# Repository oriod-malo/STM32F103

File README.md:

# STM32F103 Custom Kit

My first PCB project in KiCad. 

A custom STM32F103 kit with header pins, USB connector and LED.

Very useful to get handy with KiCad.

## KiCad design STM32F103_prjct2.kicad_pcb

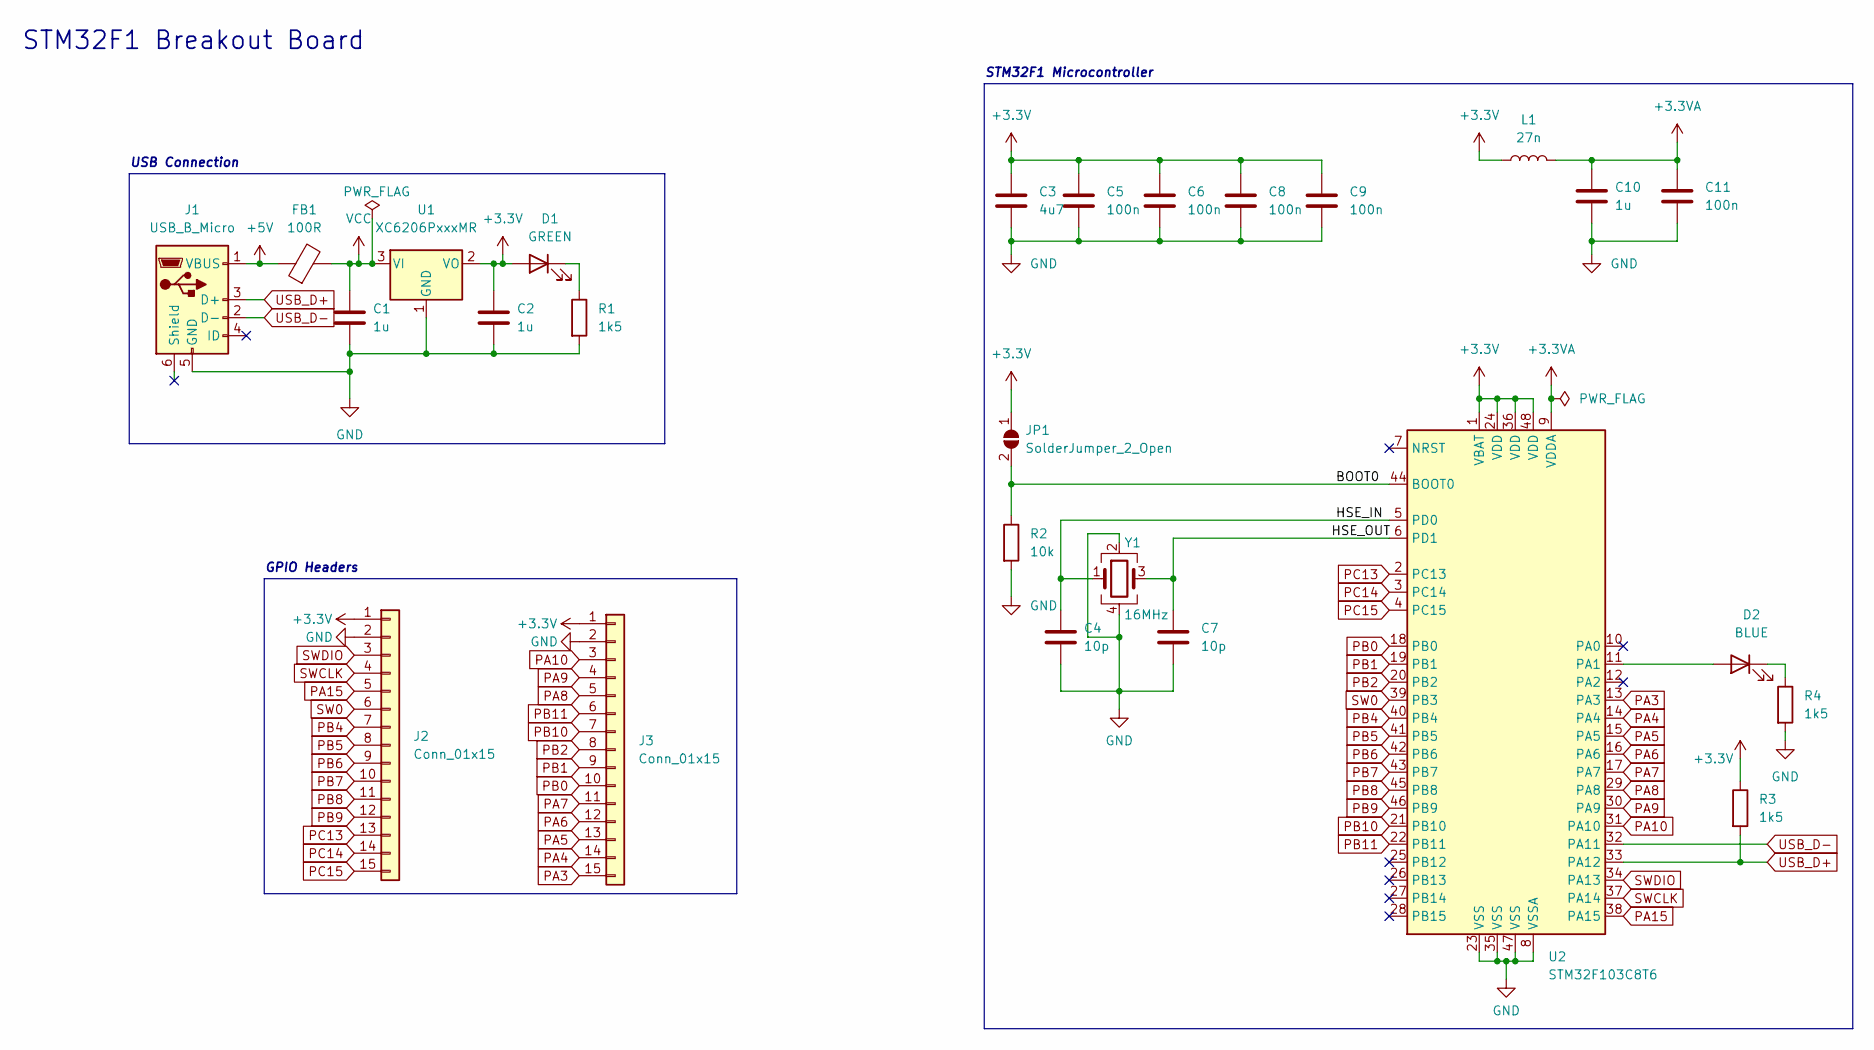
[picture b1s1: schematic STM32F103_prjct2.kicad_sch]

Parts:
C1, C2: 1u; C_0603_1608Metric
C3: 4u7; C_0603_1608Metric
C4, C7: 10p; C_0402_1005Metric
C5, C6, C8, C9, C11: 100n; C_0402_1005Metric
C10: 1u; C_0402_1005Metric
D1: GREEN; LED_0603_1608Metric
D2: BLUE; LED_0603_1608Metric
FB1: 100R; L_0805_2012Metric
J1: USB_B_Micro; USB_Micro-B_Wuerth_629105150521
J2, J3: Conn_01x15; PinHeader_1x15_P2.54mm_Vertical
JP1: SolderJumper_2_Open; SolderJumper-2_P1.3mm_Open_Pad1.0x1.5mm
L1: 27n; L_0402_1005Metric
R1, R3: 1k5; R_0603_1608Metric
R2: 10k; R_0402_1005Metric
R4: 1k5; R_0402_1005Metric
U1: XC6206PxxxMR; SOT-23
U2: STM32F103C8T6; LQFP-48_7x7mm_P0.5mm
Y1: 16MHz; Crystal_SMD_3225-4Pin_3.2x2.5mm

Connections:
+3.3V: C2.1, C3.1, C5.1, C6.1, C8.1, C9.1, D1.2 (A), J2.1, J3.1, JP1.1 (A), L1.1, R3.1, U1.2 (VO), U2.1 (VBAT), U2.24 (VDD), U2.36 (VDD), U2.48 (VDD)
+3.3VA: C10.1, C11.1, L1.2, U2.9 (VDDA)
+5V: FB1.1, J1.1 (VBUS)
/BOOT0: JP1.2 (B), R2.1, U2.44 (BOOT0)
/HSE_IN: C4.1, U2.5 (PD0), Y1.1
/HSE_OUT: C7.1, U2.6 (PD1), Y1.3
GND: C1.2, C2.2, C3.2, C4.2, C5.2, C6.2, C7.2, C8.2, C9.2, C10.2, C11.2, J1.5 (GND), J2.2, J3.2, R1.2, R2.2, R4.2, U1.1 (GND), U2.8 (VSSA), U2.23 (VSS), U2.35 (VSS), U2.47 (VSS), Y1.2, Y1.4
unnamed: D1.1 (K), R1.1
unnamed: D2.1 (K), R4.1
unnamed: D2.2 (A), U2.11 (PA1)
PA3: J3.15, U2.13 (PA3)
PA4: J3.14, U2.14 (PA4)
PA5: J3.13, U2.15 (PA5)
PA6: J3.12, U2.16 (PA6)
PA7: J3.11, U2.17 (PA7)
PA8: J3.5, U2.29 (PA8)
PA9: J3.4, U2.30 (PA9)
PA10: J3.3, U2.31 (PA10)
PA15: J2.5, U2.38 (PA15)
PB0: J3.10, U2.18 (PB0)
PB1: J3.9, U2.19 (PB1)
PB2: J3.8, U2.20 (PB2)
PB4: J2.7, U2.40 (PB4)
PB5: J2.8, U2.41 (PB5)
PB6: J2.9, U2.42 (PB6)
PB7: J2.10, U2.43 (PB7)
PB8: J2.11, U2.45 (PB8)
PB9: J2.12, U2.46 (PB9)
PB10: J3.7, U2.21 (PB10)
PB11: J3.6, U2.22 (PB11)
PC13: J2.13, U2.2 (PC13)
PC14: J2.14, U2.3 (PC14)
PC15: J2.15, U2.4 (PC15)
SW0: J2.6, U2.39 (PB3)
SWCLK: J2.4, U2.37 (PA14)
SWDIO: J2.3, U2.34 (PA13)
USB_D+: J1.3 (D+), R3.2, U2.33 (PA12)
USB_D-: J1.2 (D-), U2.32 (PA11)
VCC: C1.1, FB1.2, U1.3 (VI)

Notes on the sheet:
STM32F1 Microcontroller
USB Connection
GPIO Headers
STM32F1 Breakout Board

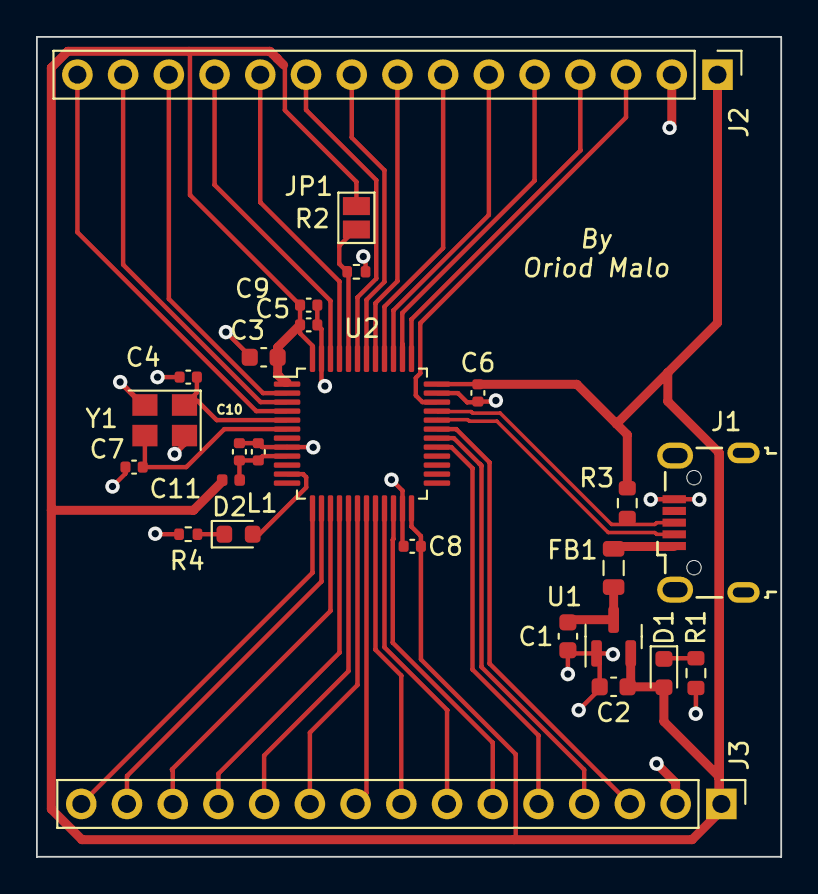
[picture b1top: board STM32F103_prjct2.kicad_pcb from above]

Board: 2 copper layers, 41.3 x 45.5 mm, 26 parts (0 on the bottom side), 39 nets.

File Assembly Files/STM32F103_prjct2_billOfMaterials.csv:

"Source:","C:\Users\CTS\Documents\KiCad\6.0\projects\STM32F103_prjct2\STM32F103_prjct2.kicad_sch"
"Date:","3/20/2023 7:13:50 PM"
"Tool:","Eeschema (6.0.9)"
"Generator:","C:\Program Files\KiCad\6.0\bin\scripting\plugins/bom_csv_grouped_by_value.py"
"Component Count:","26"

"Individual Components:"

"Item","Qty","Reference(s)","Value","LibPart","Footprint","Datasheet"
"","","C1","1u","Device:C","Capacitor_SMD:C_0603_1608Metric","~"
"","","C2","1u","Device:C","Capacitor_SMD:C_0603_1608Metric","~"
"","","C3","4u7","Device:C","Capacitor_SMD:C_0603_1608Metric","~"
"","","C4","10p","Device:C","Capacitor_SMD:C_0402_1005Metric","~"
"","","C5","100n","Device:C","Capacitor_SMD:C_0402_1005Metric","~"
"","","C6","100n","Device:C","Capacitor_SMD:C_0402_1005Metric","~"
"","","C7","10p","Device:C","Capacitor_SMD:C_0402_1005Metric","~"
"","","C8","100n","Device:C","Capacitor_SMD:C_0402_1005Metric","~"
"","","C9","100n","Device:C","Capacitor_SMD:C_0402_1005Metric","~"
"","","C10","1u","Device:C","Capacitor_SMD:C_0402_1005Metric","~"
"","","C11","100n","Device:C","Capacitor_SMD:C_0402_1005Metric","~"
"","","D1","GREEN","Device:LED","LED_SMD:LED_0603_1608Metric","~"
"","","D2","BLUE","Device:LED","LED_SMD:LED_0603_1608Metric","~"
"","","FB1","100R","Device:FerriteBead","Inductor_SMD:L_0805_2012Metric","~"
"","","J1","USB_B_Micro","Connector:USB_B_Micro","Connector_USB:USB_Micro-B_Wuerth_629105150521","~"
"","","J2","Conn_01x15","Connector_Generic:Conn_01x15","Connector_PinHeader_2.54mm:PinHeader_1x15_P2.54mm_Vertical","~"
"","","J3","Conn_01x15","Connector_Generic:Conn_01x15","Connector_PinHeader_2.54mm:PinHeader_1x15_P2.54mm_Vertical","~"
"","","JP1","SolderJumper_2_Open","Jumper:SolderJumper_2_Open","Jumper:SolderJumper-2_P1.3mm_Open_Pad1.0x1.5mm","~"
"","","L1","27n","Device:L","Inductor_SMD:L_0402_1005Metric","~"
"","","R1","1k5","Device:R","Resistor_SMD:R_0603_1608Metric","~"
"","","R2","10k","Device:R","Resistor_SMD:R_0402_1005Metric","~"
"","","R3","1k5","Device:R","Resistor_SMD:R_0603_1608Metric","~"
"","","R4","1k5","Device:R","Resistor_SMD:R_0402_1005Metric","~"
"","","U1","XC6206PxxxMR","Regulator_Linear:XC6206PxxxMR","Package_TO_SOT_SMD:SOT-23","https://www.torexsemi.com/file/xc6206/XC6206.pdf"
"","","U2","STM32F103C8T6","MCU_ST_STM32F1:STM32F103C8Tx","Package_QFP:LQFP-48_7x7mm_P0.5mm","http://www.st.com/st-web-ui/static/active/en/resource/techni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"
"","","Y1","16MHz","Device:Crystal_GND24","Crystal:Crystal_SMD_3225-4Pin_3.2x2.5mm","~"



"Collated Components:"

"Item","Qty","Reference(s)","Value","LibPart","Footprint","Datasheet"
"1","2","C1, C2","1u","Device:C","Capacitor_SMD:C_0603_1608Metric","~"
"2","1","C3","4u7","Device:C","Capacitor_SMD:C_0603_1608Metric","~"
"3","2","C4, C7","10p","Device:C","Capacitor_SMD:C_0402_1005Metric","~"
"4","5","C5, C6, C8, C9, C11","100n","Device:C","Capacitor_SMD:C_0402_1005Metric","~"
"5","1","C10","1u","Device:C","Capacitor_SMD:C_0402_1005Metric","~"
"6","1","D1","GREEN","Device:LED","LED_SMD:LED_0603_1608Metric","~"
"7","1","D2","BLUE","Device:LED","LED_SMD:LED_0603_1608Metric","~"
"8","1","FB1","100R","Device:FerriteBead","Inductor_SMD:L_0805_2012Metric","~"
"9","1","J1","USB_B_Micro","Connector:USB_B_Micro","Connector_USB:USB_Micro-B_Wuerth_629105150521","~"
"10","2","J2, J3","Conn_01x15","Connector_Generic:Conn_01x15","Connector_PinHeader_2.54mm:PinHeader_1x15_P2.54mm_Vertical","~"
"11","1","JP1","SolderJumper_2_Open","Jumper:SolderJumper_2_Open","Jumper:SolderJumper-2_P1.3mm_Open_Pad1.0x1.5mm","~"
"12","1","L1","27n","Device:L","Inductor_SMD:L_0402_1005Metric","~"
"13","2","R1, R3","1k5","Device:R","Resistor_SMD:R_0603_1608Metric","~"
"14","1","R2","10k","Device:R","Resistor_SMD:R_0402_1005Metric","~"
"15","1","R4","1k5","Device:R","Resistor_SMD:R_0402_1005Metric","~"
"16","1","U1","XC6206PxxxMR","Regulator_Linear:XC6206PxxxMR","Package_TO_SOT_SMD:SOT-23","https://www.torexsemi.com/file/xc6206/XC6206.pdf"
"17","1","U2","STM32F103C8T6","MCU_ST_STM32F1:STM32F103C8Tx","Package_QFP:LQFP-48_7x7mm_P0.5mm","http://www.st.com/st-web-ui/static/active/en/resource/techni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"
"18","1","Y1","16MHz","Device:Crystal_GND24","Crystal:Crystal_SMD_3225-4Pin_3.2x2.5mm","~"
